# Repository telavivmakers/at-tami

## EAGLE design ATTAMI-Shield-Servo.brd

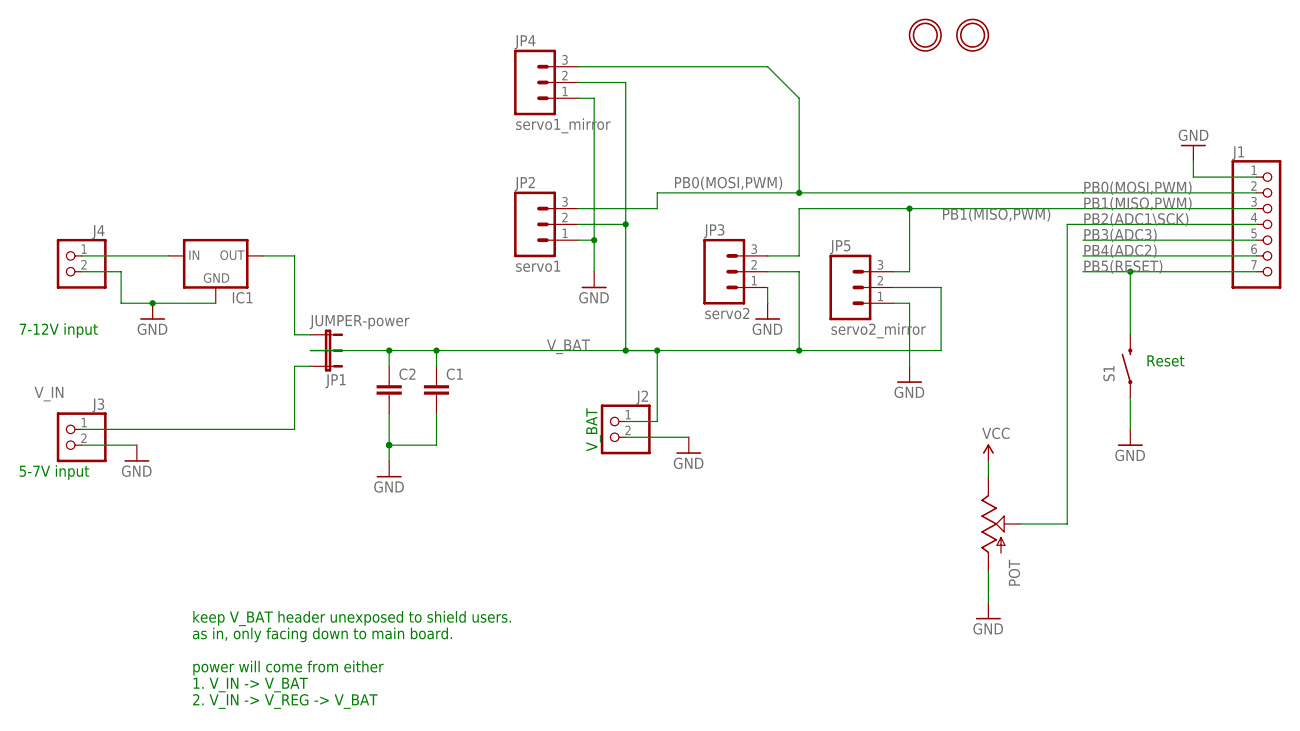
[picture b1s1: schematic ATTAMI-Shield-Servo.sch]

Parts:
C1, C2: CAPKIT; CAP-PTH-SMALL-KIT
IC1: V_REG_78XXSINK; TO220-IGO
J1: HEADER-1X7ROUND; 1X07_ROUND
J2, J3, J4: HEADER-1X2ROUND; 1X02_ROUND
JP1: JUMPER-power; 1X03
JP2: servo1; 1X03_LONGPADS
JP3: servo2; 1X03_LONGPADS
JP4: servo1_mirror; 1X03_LONGPADS
JP5: servo2_mirror; 1X03_LONGPADS
POT: POT100K_3362U; 3362U
S1: SWITCH-MOMENTARY-2-SMD-1101NE; TACTILE-SWITCH-1101NE
U$1, U$2: MOUNTINGHOLE2.0; MOUNTINGHOLE_2.0_PLATED

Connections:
GND: C1.2, C2.2, IC1.GND, J1.1, J2.2, J3.2, J4.2, JP2.1, JP3.1, JP4.1, JP5.1, POT.P$3 (A), S1.P$1 (1)
unnamed: IC1.IN, J4.1
unnamed: IC1.OUT, JP1.3
PB0(MOSI,PWM): J1.2, JP2.3, JP4.3
PB1(MISO,PWM): J1.3, JP3.3, JP5.3
PB2(ADC1\SCK): J1.4, POT.P$2 (S)
PB3(ADC3): J1.5
PB4(ADC2): J1.6
PB5(RESET): J1.7, S1.P$2 (2)
VCC: POT.P$1 (E)
V_BAT: C1.1, C2.1, J2.1, JP1.2, JP2.2, JP3.2, JP4.2, JP5.2
V_IN: J3.1, JP1.1

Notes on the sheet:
V_BAT
5-7V input
keep V_BAT header unexposed to shield users. as in, only facing down to main board. power will come from either 1. V_IN -> V_BAT 2. V_IN -> V_REG -> V_BAT
7-12V input
Reset

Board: 2 copper layers, 17 parts (0 on the bottom side), 9 nets, no tracks yet.

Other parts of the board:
U$3: OSHW_6X150_NOTEXT

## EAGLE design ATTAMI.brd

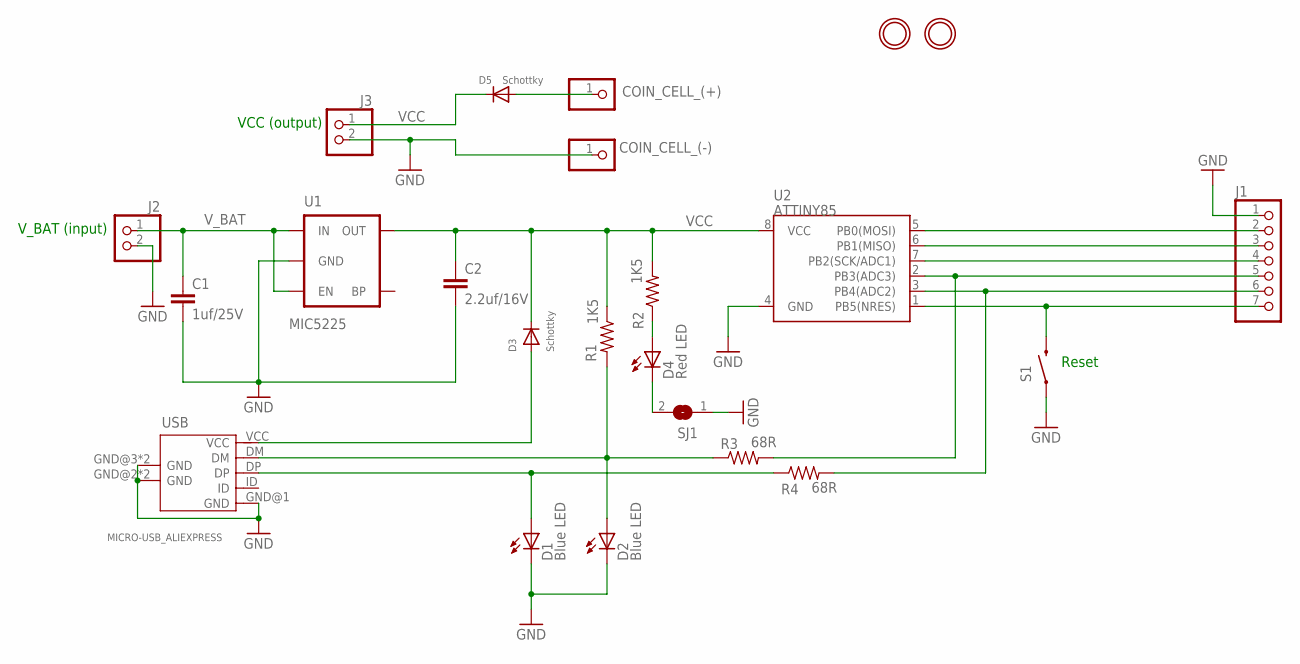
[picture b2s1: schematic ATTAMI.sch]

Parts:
C1: 1uf/25V; 0805
C2: 2.2uf/16V; 0805
COIN_CELL_(+): PINHD-1X1CB; 1X01-CLEANBIG
COIN_CELL_(-): PINHD-1X1CB; 1X01-CLEANBIG
D1, D2: Blue LED; LED-805
D3, D5: Schottky; SOD-323
D4: Red LED; LED-805
J1: HEADER-1X7ROUND; 1X07_ROUND
J2, J3: HEADER-1X2ROUND; 1X02_ROUND
R1, R2: 1K5; 0805
R3, R4: 68R; 0805
S1: SWITCH-MOMENTARY-2-SMD-1101NE; TACTILE-SWITCH-1101NE
SJ1: SOLDERJUMPERCLOSED; SOLDERJUMPER_CLOSEDWIRE
U1: MIC5225; SOT23-5
U2: ATTINY85; SO08-EIAJ
U$1, U$2: MOUNTINGHOLE2.0; MOUNTINGHOLE_2.0_PLATED
USB: MICRO-USB_ALIEXPRESS; USB-MICRO-ALIEXPRESS

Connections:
GND: C1.2, C2.2, COIN_CELL_(-).1, D1.C, D2.C, J1.1, J2.2, J3.2, S1.P$1 (1), SJ1.1, U1.2 (GND), U2.4 (GND), USB.GND@1 (GND), USB.GND@2 (GND), USB.GND@3 (GND), USB.P$9 (GND), USB.P$10 (GND)
unnamed: J1.5, R3.2, U2.2 (PB3(ADC3))
unnamed: J1.2, U2.5 (PB0(MOSI))
unnamed: COIN_CELL_(+).1, D5.AQ (A)
unnamed: J1.4, U2.7 (PB2(SCK/ADC1))
unnamed: J1.6, R4.2, U2.3 (PB4(ADC2))
unnamed: D1.A, R4.1, USB.DP
unnamed: J1.7, S1.P$2 (2), U2.1 (PB5(NRES))
unnamed: D2.A, R1.2, R3.1, USB.DM
unnamed: D4.A, R2.1
unnamed: D4.C, SJ1.2
unnamed: J1.3, U2.6 (PB1(MISO))
V-BUS: D3.AQ (A), USB.VCC
VCC: C2.1, D3.CQ (C), D5.CQ (C), J3.1, R1.1, R2.2, U1.5 (OUT), U2.8 (VCC)
V_BAT: C1.1, J2.1, U1.1 (IN), U1.3 (EN)

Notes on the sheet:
VCC (output)
V_BAT (input)
Reset

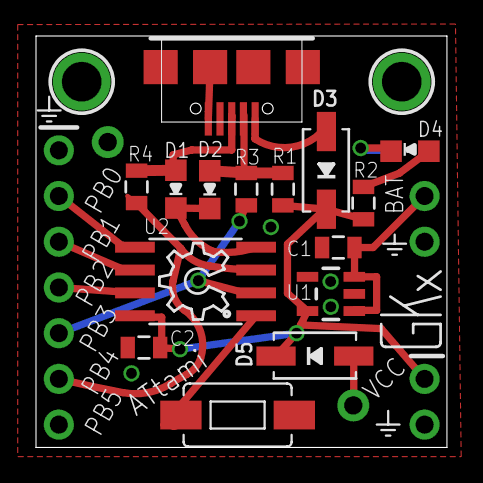
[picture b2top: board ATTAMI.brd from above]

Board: 2 copper layers, 22.8 x 22.9 mm, 24 parts (1 on the bottom side), 15 nets.

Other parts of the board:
U$3: OSHW_6X150_NOTEXT

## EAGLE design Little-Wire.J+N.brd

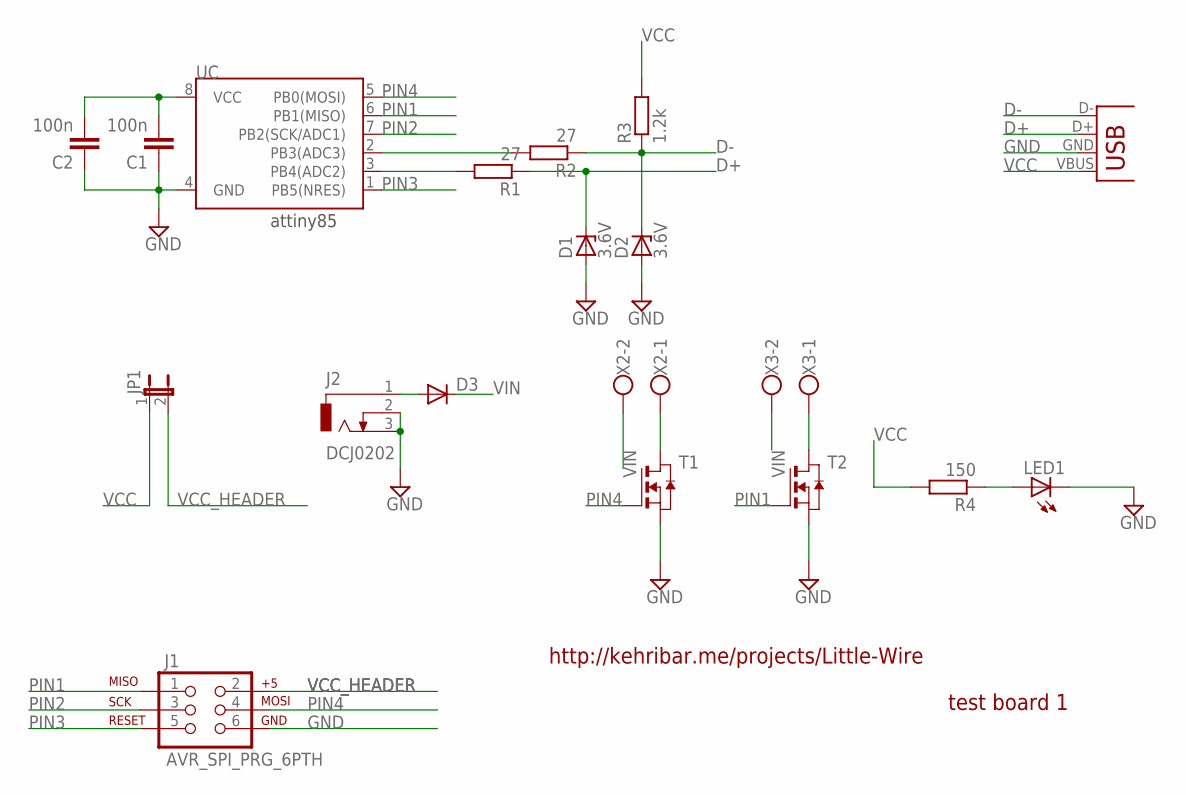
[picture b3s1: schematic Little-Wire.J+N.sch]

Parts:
C1, C2: 100n; C050-025X075
D1, D2: 3.6V; ZDIO-5
D3: DIODE-D-7.5; D-7.5
J1: AVR_SPI_PRG_6PTH; 2X3
J2: DCJ0202
JP1: JUMPER-2PTH; 1X02
LED1: LED3MM
R1, R2: 27; 0204/5
R3: 1.2k; 0204/5
R4: 150; 0204/5
T1, T2: NMOSSOT223; SOT223
UC: ATTINY45DIP8; DIP08
X1: USB-A-H
X2, X3: W237-102

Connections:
D+: D1.C, R1.1, X1.D+ (D-)
D-: D2.C, R2.1, R3.1, X1.D- (D+)
EXT1: T1.2 (D), T1.4 (D), X2.1
EXT2: T2.2 (D), T2.4 (D), X3.1
GND: C1.1, C2.1, D1.A, D2.A, J1.6, J2.2, J2.3, LED1.K (C), T1.3 (S), T2.3 (S), UC.4 (GND), X1.GND (VBUS)
unnamed: R2.2, UC.2 (PB3(ADC3))
unnamed: R1.2, UC.3 (PB4(ADC2))
unnamed: LED1.A, R4.1
unnamed: D3.A, J2.1
PIN1: J1.1, T2.1 (G), UC.6 (PB1(MISO))
PIN2: J1.3, UC.7 (PB2(SCK/ADC1))
PIN3: J1.5, UC.1 (PB5(NRES))
PIN4: J1.4, T1.1 (G), UC.5 (PB0(MOSI))
VCC: C1.2, C2.2, JP1.1, R3.2, R4.2, UC.8 (VCC), X1.VBUS (GND)
VCC_HEADER: J1.2, JP1.2
VIN: D3.C, X2.2, X3.2

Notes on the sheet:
attiny85
http://kehribar.me/projects/Little-Wire
test board 1

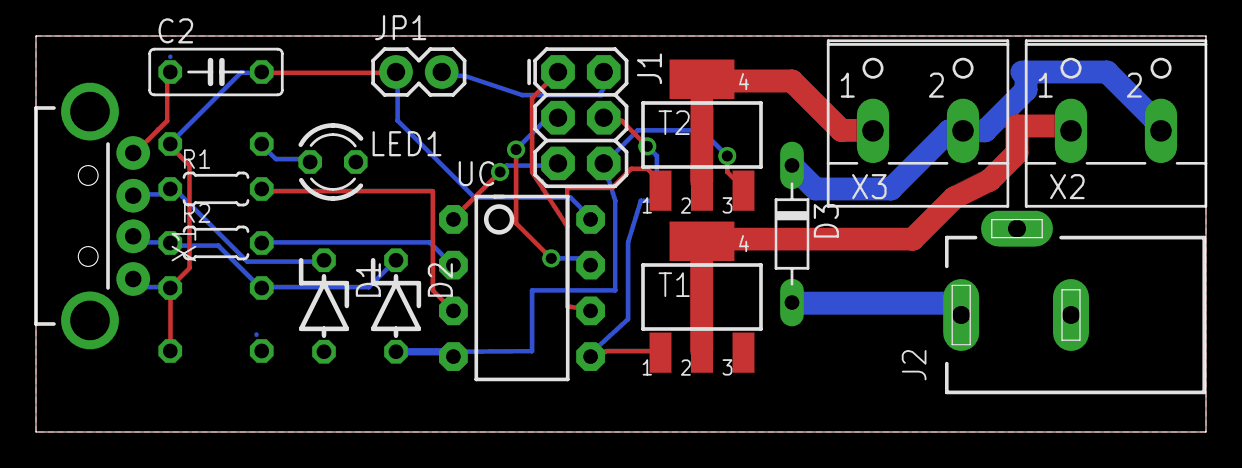
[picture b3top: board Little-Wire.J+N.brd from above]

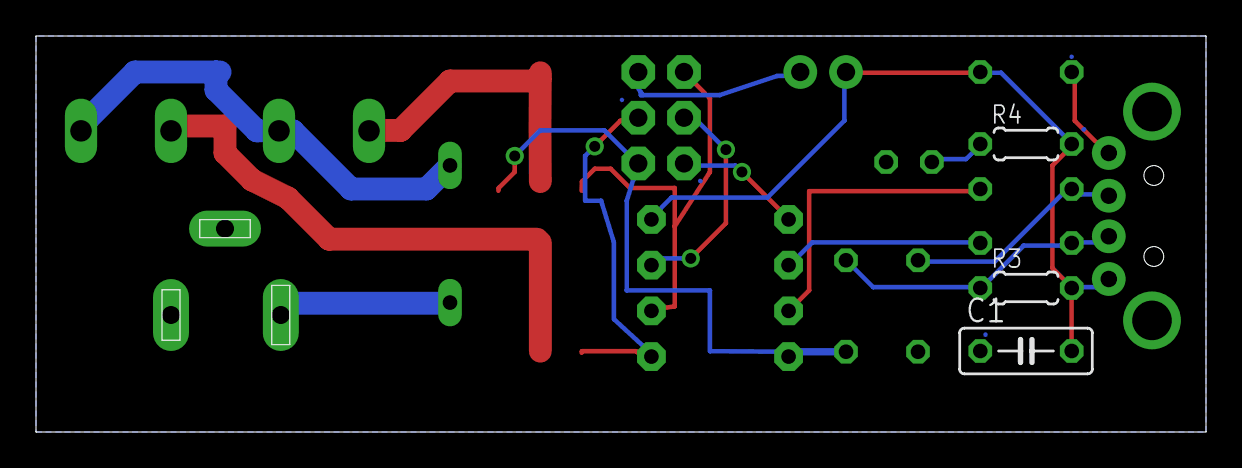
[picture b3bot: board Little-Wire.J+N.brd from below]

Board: 2 copper layers, 65.0 x 22.0 mm, 19 parts (3 on the bottom side), 16 nets.

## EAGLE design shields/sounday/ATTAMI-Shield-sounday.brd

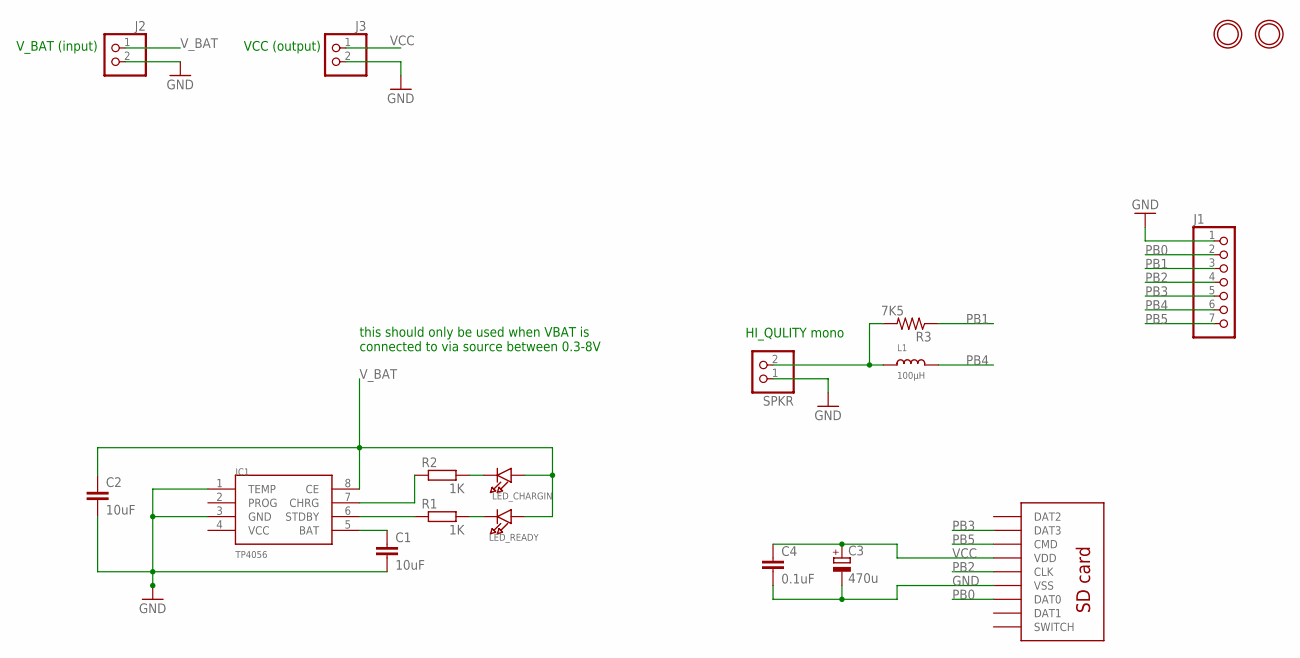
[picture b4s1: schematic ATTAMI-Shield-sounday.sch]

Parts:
C1, C2: 10uF; 1206
C3: 470u; CASE_A
C4: 0.1uF; 0603-CAP
IC1: TP4056; SOP-8
J1: HEADER-1X7ROUND; 1X07_ROUND
J2, J3: HEADER-1X2ROUND; 1X02_ROUND
L1: 100µH; 0805
LED_CHARGIN: LED0805_NOOUTLINE; CHIPLED_0805_NOOUTLINE
LED_READY: LED0805_NOOUTLINE; CHIPLED_0805_NOOUTLINE
R1, R2: 1K; R603
R3: 7K5; 0805
SPKR: HEADER-1X2ROUND; 1X02_ROUND
U$1, U$2: MOUNTINGHOLE2.0; MOUNTINGHOLE_2.0_PLATED
U$4: MOLEX-SD-105027; MOLEX-SD-105027-PKG

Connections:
GND: C1.2, C2.2, C3.-, C4.2, IC1.1 (TEMP), IC1.3 (GND), J1.1, J2.2, J3.2, SPKR.1, U$4.P$6 (VSS)
unnamed: C1.1, IC1.5 (BAT)
unnamed: LED_CHARGIN.C, R2.2
unnamed: LED_READY.C, R1.2
unnamed: IC1.6 (STDBY), R1.1
unnamed: IC1.7 (CHRG), R2.1
unnamed: L1.1, R3.2, SPKR.2
PB0: J1.2, U$4.P$7 (DAT0)
PB1: J1.3, R3.1
PB2: J1.4, U$4.P$5 (CLK)
PB3: J1.5, U$4.P$2 (DAT3)
PB4: J1.6, L1.2
PB5: J1.7, U$4.P$3 (CMD)
VCC: C3.+, C4.1, J3.1, U$4.P$4 (VDD)
V_BAT: C2.1, IC1.8 (CE), J2.1, LED_CHARGIN.A, LED_READY.A

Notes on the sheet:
VCC (output)
V_BAT (input)
this should only be used when VBAT is connected to via source between 0.3-8V
HI_QULITY mono

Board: 2 copper layers, 19 parts (0 on the bottom side), 15 nets, no tracks yet.

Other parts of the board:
U$3: OSHW_6X150_NOTEXT

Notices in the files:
ATTAMI-Shield-Servo.sch:
LICENSE: CERN OHL 1.7
parts and their libraries:
microbuilder: This work is placed in the public domain, and may be freely used for commercial and non-commercial work with the following conditions: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
SparkFun-Connectors: Licensing: CC v3.0 Share-Alike You are welcome to use this library for commercial purposes.
